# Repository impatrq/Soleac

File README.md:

<!DOCTYPE html>
<html>
<head>
    <meta charset="UTF-8">

</head>
<body>
    <h1><strong>Soleac</strong></h1>
<p align="center">
  
  &nbsp;&nbsp;&nbsp;&nbsp;
  
</p>
    </body> 
  <h2><strong>Logros y Reconocimientos</strong></h2>
<li>🏅 <b>Ganadores del 1° puesto en la categoría Prototipos: Seguridad y Protección - ONIET 2026</b> (puntaje: 90/100)  </li>
📍 Representando a la <b>E.E.S.T. N°7 “Taller Regional Quilmes”</b>, Buenos Aires, Argentina
</body>
  <h2><strong>Organizacion de archivos</strong></h2>
<em><li><b>Carpeta de campo</b>/Progreso y documentacion </li>
<li><b>Diseño 3D</b>/Diseños fisicos de herraminetas</li>
<li><b>Firmware</b>/Codigos implementados a los microcontroladores</li>
<li><b>Hardware</b></Esquematicos y PCBs</li>
<li><b>Assets</b>/Logotipos, README lockup</li></em>
<hr>
<body>
    <h2><strong>Que es Soleac y cómo funciona</strong></h2>
   <em><b>Soleac es un instrumento tecnologico detector de fugas de aire comprimido y gas. 
   <br>Mediante receptores de frecuencia tales cómo:</b>
   <li>Microfono MEMS SPH0641LU4H-1</li>
    <li>MURATA MA40S4R</li>
<b>Podemos captar fugas en caños, ya que estas generan una frecuencia de entre 20khz y 80khz dependiendo el tamaño.<br>Mediante el siguiente sensor:</b>
 <li>Sensor de gas MQ-9</li>
 <b>Al acercar el instrumento, este sensor confirma si realmente hay una fuga, cabe aclarar que solo funciona sensando los siguientes gases:</b>
 <ul>
  <li>Gas Licuado de Petróleo</li>
  <li>Propano</li>
  <li>Metano</li>
  <li>Monóxido de carbono</li>
    <li>butano</li>
</ul>
<b>Si quisieras captar aire comprimido con este sensor, por ejemplo, no sirve y tendrias que usar los sensores de frecuencia.</b></em>
<hr>
<body>
    <h2><strong>Porque existe Soleac</strong></h2>
    <em><b>El instrumento Soleac surge de tres problematicas actuales:</b><br>
    La primera y mas importante es que solo existe una herramienta para los plomeros que les indique con precision donde hay una fuga sin tener que romper ni un ladrillo de pared, la problematica de esta herramienta es que es demasiado cara y ahi es donde entra soleac, presentando un precio que por lo menos este en el presupuesto de un plomero promedio. Llevando a estas herramientas detectores de fugas no solo a empresas grandes, si no tambien a empresas chicas y hogares.</em>
<hr>
<body>
    <h2><strong>Modelo Soleac</strong></h2>

<hr>
<body>
  <h2><strong>Componentes principales del proyecto</strong></h2>
  <em><li>Esp32 S3 Touch Lcd 3.5B</li>
  <li>Microfono MEMS SPH0641LU4H-1</li>
  <li>MURATA MA40S4R</li>
  <li>Sensor de gas MQ-9</li></em>
</body>
<hr>
<body>
    <h2><strong>Integrantes</strong></h2>
  <em><li>Rea Vera Jhonatan</li>
  <li>Solis Tobias</li>
  <li>Sanabria Federico</li>
  <li>Romero Julian</li>
    <li>Paolo Valentino</li></em>
</body>
<hr>

<hr>
<body>
<h3><strong>Contacto</strong></h3>
<p>
  <br>
  <br>
  
    <br>
</p>

<h3><strong>Otros proyectos</strong></h3>
<p>
  
</p>

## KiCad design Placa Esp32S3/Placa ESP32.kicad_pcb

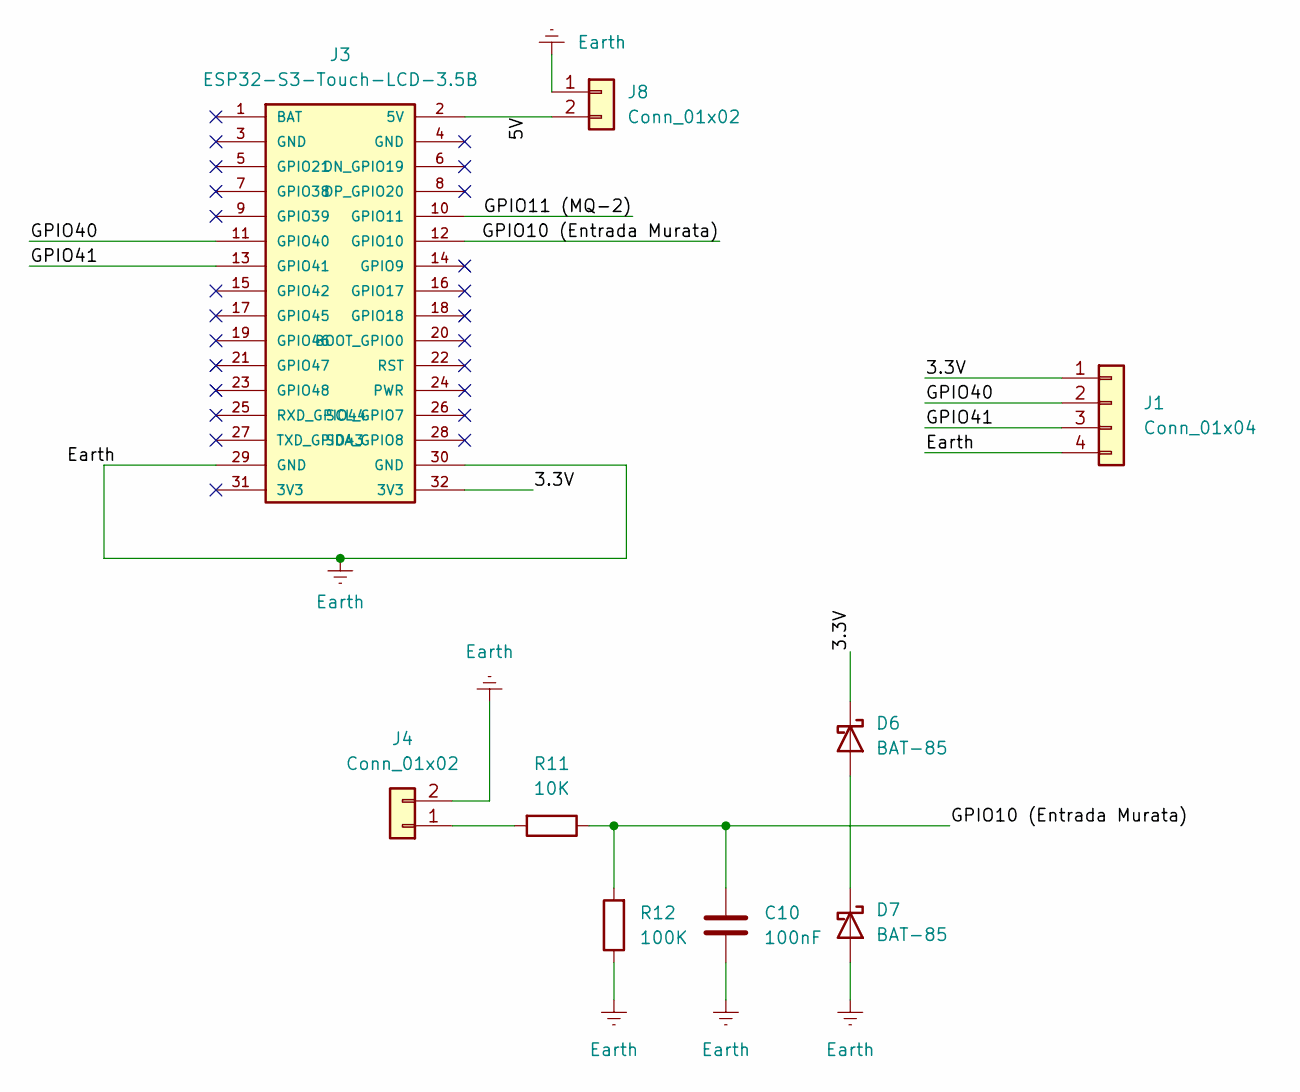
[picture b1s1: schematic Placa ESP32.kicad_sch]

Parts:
C10: 100nF; C_Radial_D6.3mm_H11.0mm_P2.50mm
D6, D7: BAT-85; D_DO-35_SOD27_P7.62mm_Horizontal
J1: Conn_01x04; Molex_KK-254_AE-6410-04A_1x04_P2.54mm_Vertical
J3: ESP32-S3-Touch-LCD-3.5B; ESP32-S3-Touch-LCD-3.5B_Header_2x16_P2.54mm
J4, J8: Conn_01x02; Molex_KK-254_AE-6410-02A_1x02_P2.54mm_Vertical
R11: 10K; R_Axial_DIN0204_L3.6mm_D1.6mm_P7.62mm_Horizontal
R12: 100K; R_Axial_DIN0204_L3.6mm_D1.6mm_P7.62mm_Horizontal

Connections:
/3.3V: D6.1 (K), J1.1, J3.32 (3V3)
/5V: J3.2 (5V), J8.2
/GPIO10 (Entrada Murata): C10.1, J3.12 (GPIO10), R11.1, R12.2
/GPIO11 (MQ-2): J3.10 (GPIO11)
/GPIO40: J1.2, J3.11 (GPIO40)
/GPIO41: J1.3, J3.13 (GPIO41)
Earth: C10.2, D7.2 (A), J1.4, J3.29 (GND), J3.30 (GND), J4.2, J8.1, R12.1
unnamed: D6.2 (A), D7.1 (K)
unnamed: J4.1, R11.2

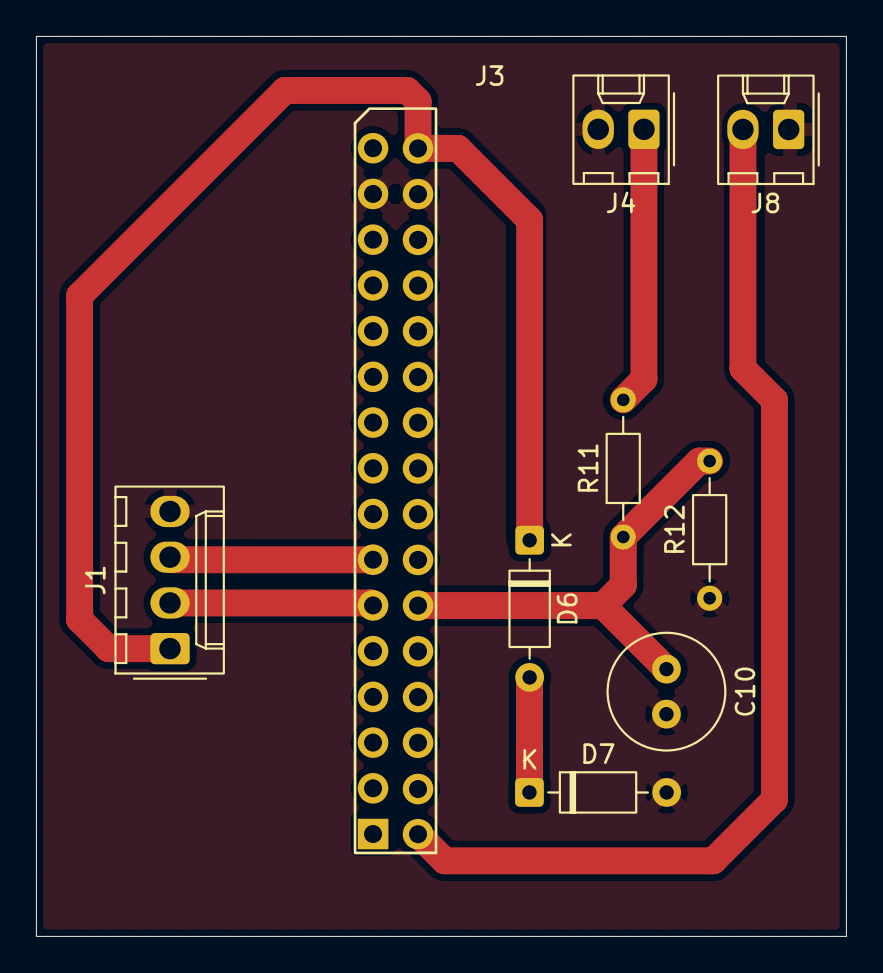
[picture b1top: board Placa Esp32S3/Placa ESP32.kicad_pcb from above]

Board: 2 copper layers, 45.0 x 50.0 mm, 9 parts (0 on the bottom side), 8 nets.

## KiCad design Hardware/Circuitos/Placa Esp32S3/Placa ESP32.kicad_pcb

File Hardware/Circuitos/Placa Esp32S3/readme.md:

## Archivos 
- `Placa ESP32-backups` Backups de la placa ESP32.
- `Placa ESP32.kicad_pcb` PCB formato kicad de la placa ESP32.
- `Placa ESP32.kicad_pro`  configuración compartida entre el editor de esquemáticos y el editor de PCB.
- `Placa ESP32.kicad_sch` diagrama esquemático de la placa ESP32.

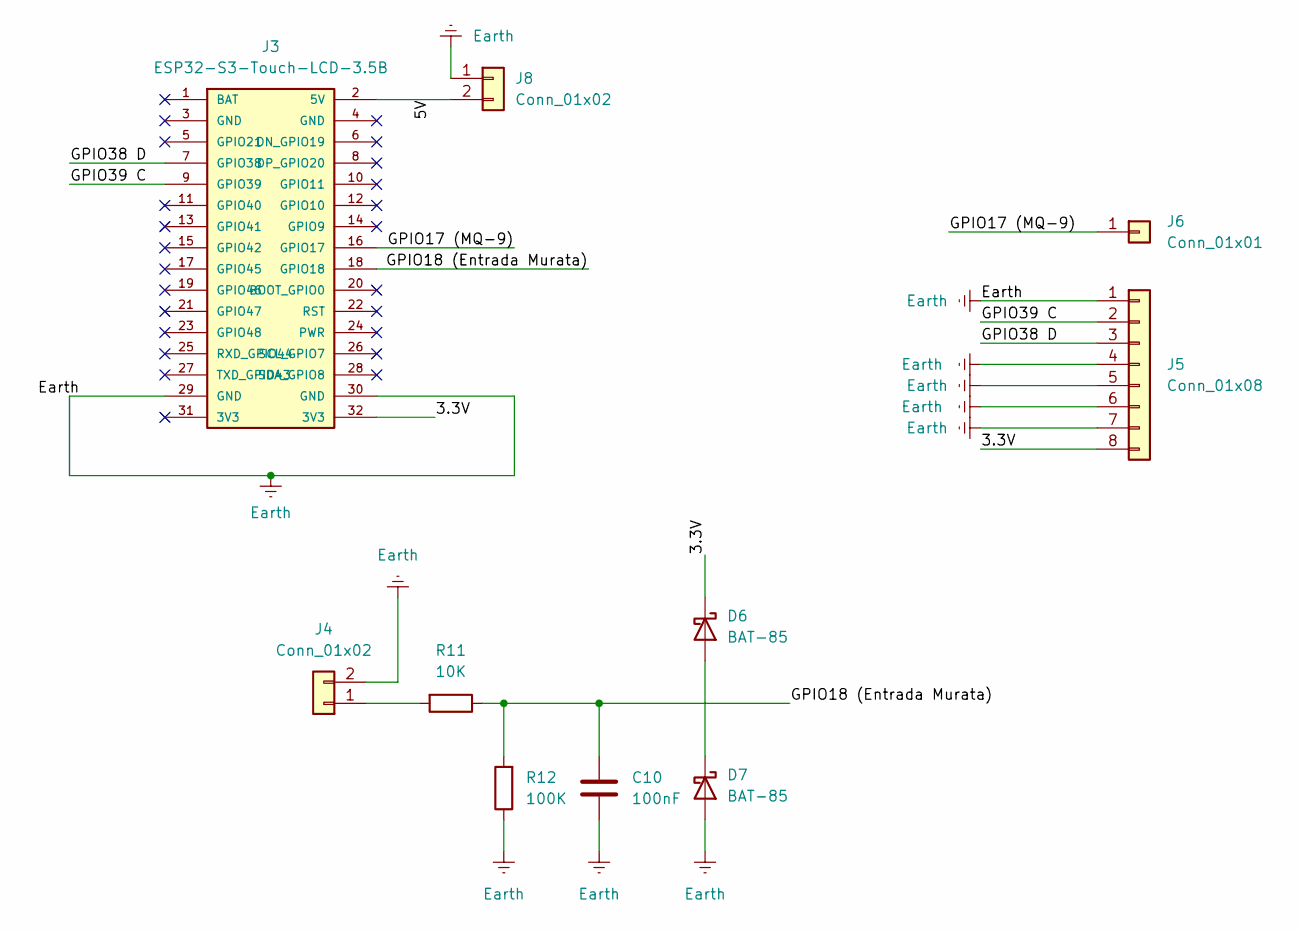
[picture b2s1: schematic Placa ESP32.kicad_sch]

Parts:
C10: 100nF; C_Radial_D6.3mm_H11.0mm_P2.50mm
D6, D7: BAT-85; D_DO-35_SOD27_P7.62mm_Horizontal
J3: ESP32-S3-Touch-LCD-3.5B; ESP32-S3-Touch-LCD-3.5B_Header_2x16_P2.54mm
J4, J8: Conn_01x02; Molex_KK-254_AE-6410-02A_1x02_P2.54mm_Vertical
J5: Conn_01x08; RJ45_Amphenol_54602-x08_Horizontal
J6: Conn_01x01; PinHeader_1x01_P2.00mm_Vertical
R11: 10K; R_Axial_DIN0204_L3.6mm_D1.6mm_P7.62mm_Horizontal
R12: 100K; R_Axial_DIN0204_L3.6mm_D1.6mm_P7.62mm_Horizontal

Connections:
/3.3V: D6.1 (K), J3.32 (3V3), J5.8
/5V: J3.2 (5V), J8.2
/GPIO17 (MQ-9): J3.16 (GPIO17), J6.1 (Pin_1_1)
/GPIO18 (Entrada Murata): C10.1, J3.18 (GPIO18), R11.1, R12.2
/GPIO38 D: J3.7 (GPIO38), J5.3
/GPIO39 C: J3.9 (GPIO39), J5.2
Earth: C10.2, D7.2 (A), J3.29 (GND), J3.30 (GND), J4.2, J5.1, J5.4, J5.5, J5.6, J5.7, J8.1, R12.1
unnamed: D6.2 (A), D7.1 (K)
unnamed: J4.1, R11.2

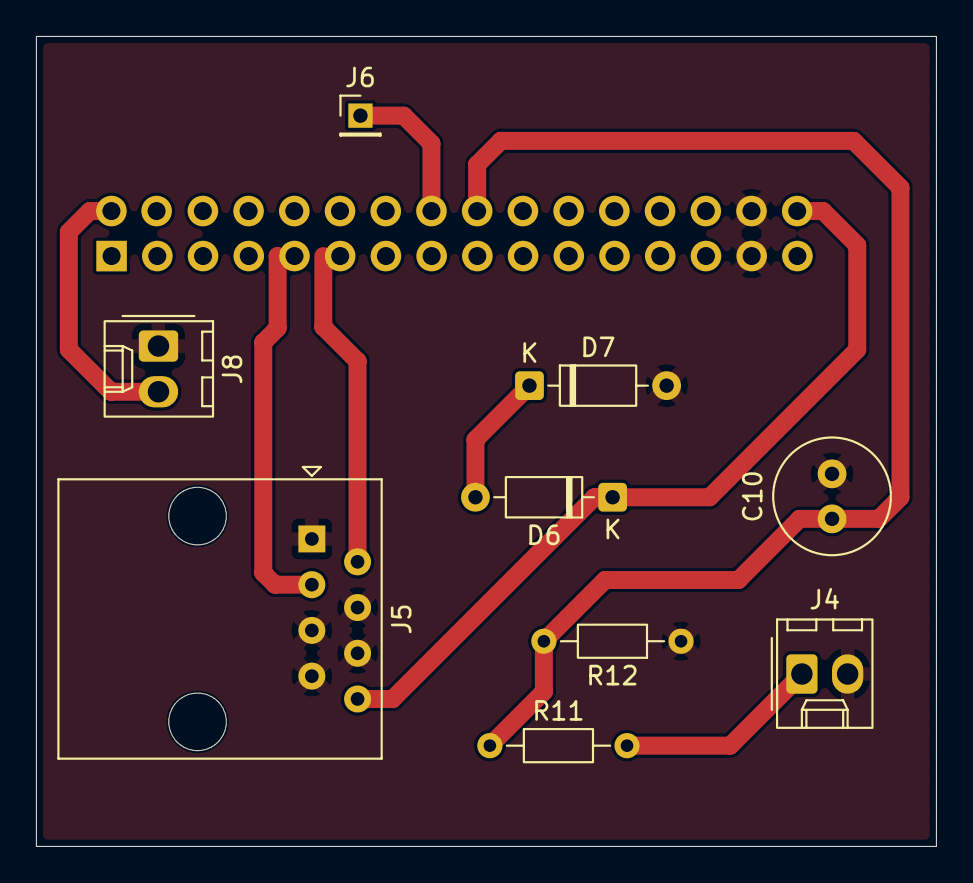
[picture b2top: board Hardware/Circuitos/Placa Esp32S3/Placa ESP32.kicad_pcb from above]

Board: 2 copper layers, 50.0 x 45.0 mm, 10 parts (1 on the bottom side), 9 nets.

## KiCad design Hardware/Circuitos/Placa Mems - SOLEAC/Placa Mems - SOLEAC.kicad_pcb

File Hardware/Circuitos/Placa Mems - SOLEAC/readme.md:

1. Archivos Backups: Historial de copias guardadas de la placa procesadora, placa de microfonos y placa esp32.
2. Remarco de placa de microfonos.
3. Placa de microfonos impresa en pdf.
4. De acá en adelante es el codigo de kicad para generar el pcb.

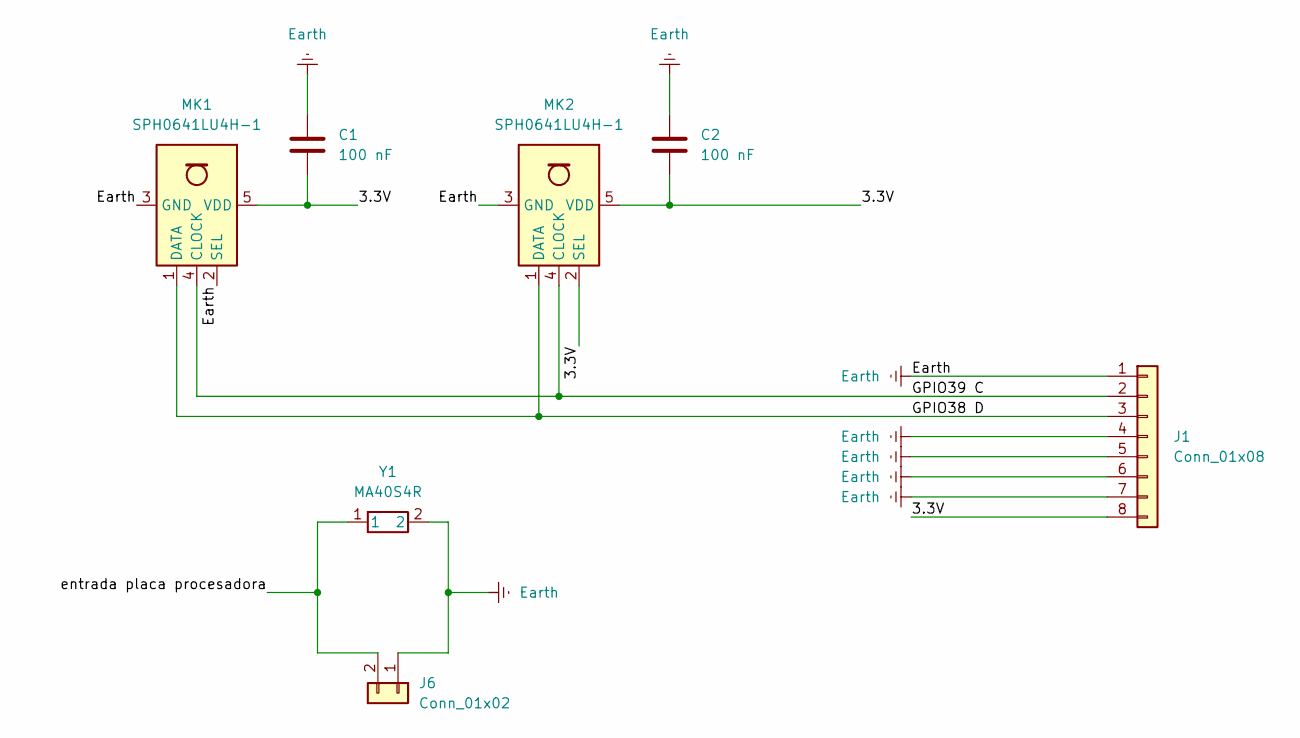
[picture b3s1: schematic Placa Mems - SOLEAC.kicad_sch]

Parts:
C1, C2: 100 nF; C_Disc_D4.3mm_W1.9mm_P5.00mm
J1: Conn_01x08; RJ45_Amphenol_54602-x08_Horizontal
J6: Conn_01x02; Molex_KK-254_AE-6410-02A_1x02_P2.54mm_Vertical
MK1, MK2: SPH0641LU4H-1; Knowles_LGA-5_3.5x2.65mm
Y1: MA40S4R; MA4024R

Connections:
/3.3V: C1.2, C2.2, J1.8, MK1.5 (VDD), MK2.2 (SEL), MK2.5 (VDD)
/GPIO38 D: J1.3, MK1.1 (DATA), MK2.1 (DATA)
/GPIO39 C: J1.2, MK1.4 (CLOCK), MK2.4 (CLOCK)
/entrada placa procesadora: J6.2, Y1.1
Earth: C1.1, C2.1, J1.1, J1.4, J1.5, J1.6, J1.7, J6.1, MK1.2 (SEL), MK1.3 (GND), MK2.3 (GND), Y1.2

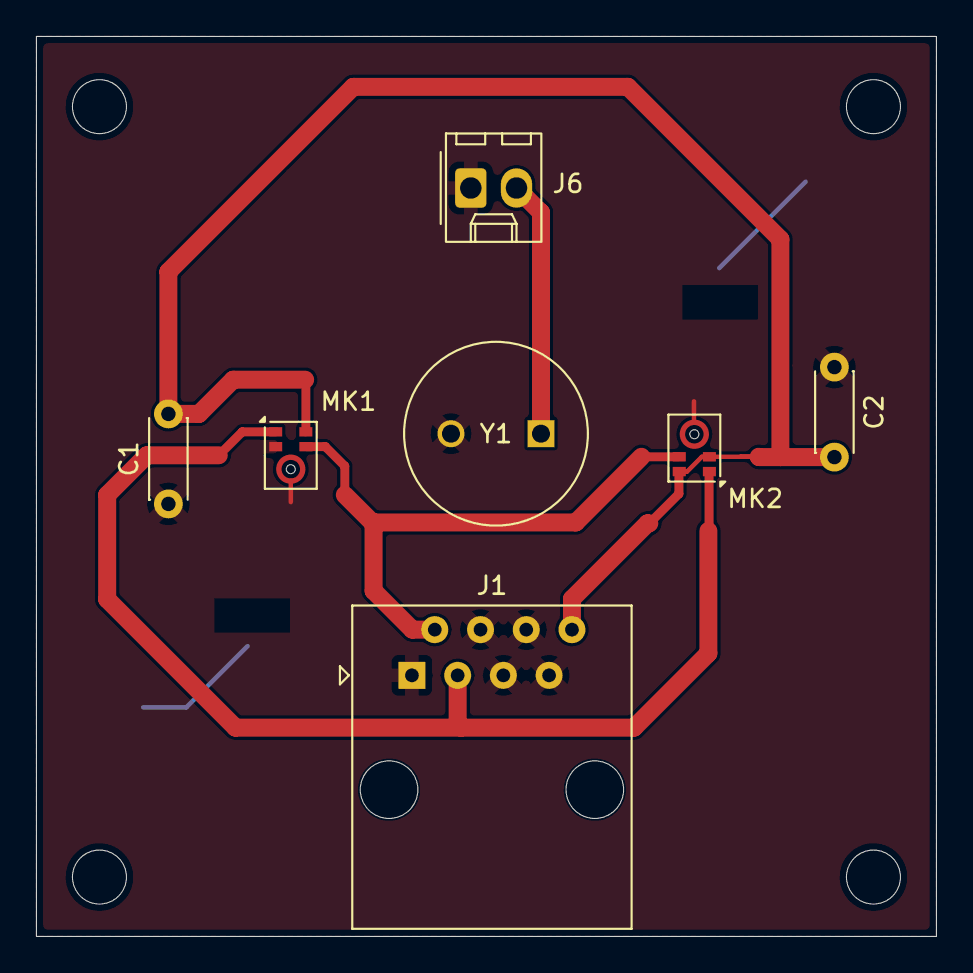
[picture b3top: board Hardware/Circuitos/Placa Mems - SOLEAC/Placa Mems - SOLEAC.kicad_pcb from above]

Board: 2 copper layers, 50.0 x 50.0 mm, 7 parts (0 on the bottom side), 5 nets.

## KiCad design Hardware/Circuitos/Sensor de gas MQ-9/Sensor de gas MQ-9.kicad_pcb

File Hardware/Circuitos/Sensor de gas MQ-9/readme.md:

## Archivos
- `Sensor de gas MQ-9-backups` Backups de la placa MQ-9.
- `Sensor de gas MQ-9.kicad_pcb` PCB formato kicad de la placa MQ-9.
- `Sensor de gas MQ-9.kicad_pro`  configuración compartida entre el editor de esquemáticos y el editor de PCB.
- `Sensor de gas MQ-9.kicad_sch` diagrama esquemático de la placa MQ-9.

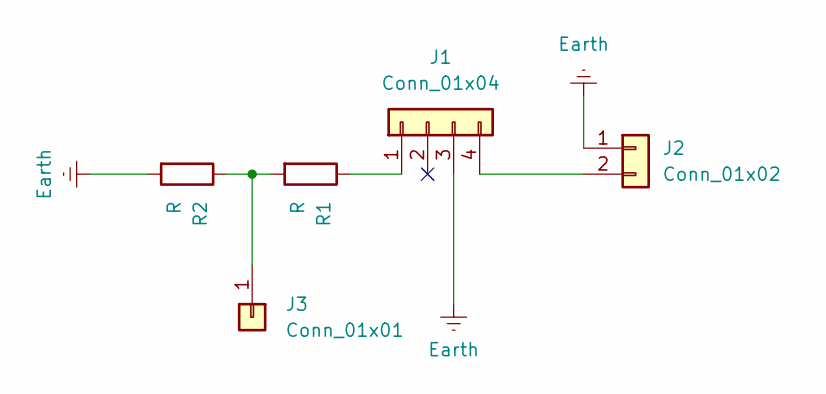
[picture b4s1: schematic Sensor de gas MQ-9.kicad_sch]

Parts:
J1: Conn_01x04; PinHeader_1x04_P2.54mm_Vertical
J2: Conn_01x02; Molex_KK-254_AE-6410-02A_1x02_P2.54mm_Vertical
J3: Conn_01x01; PinHeader_1x01_P2.00mm_Vertical
R1, R2: R; R_Axial_DIN0207_L6.3mm_D2.5mm_P7.62mm_Horizontal

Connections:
Earth: J1.3, J2.1, R2.2
unnamed: J1.1, R1.1
unnamed: J1.4, J2.2
unnamed: J3.1 (Pin_1_1), R1.2, R2.1

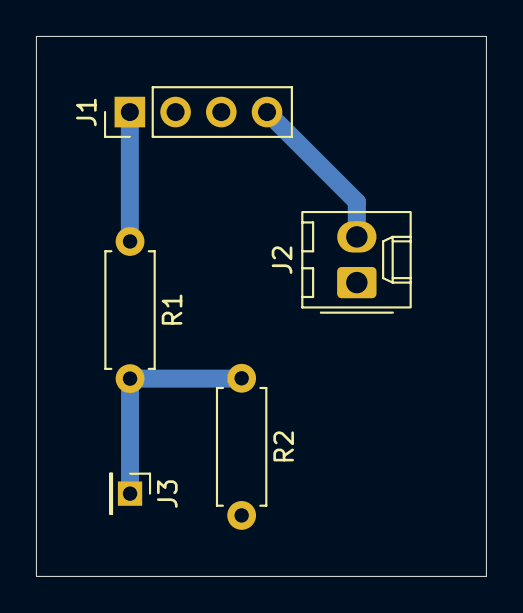
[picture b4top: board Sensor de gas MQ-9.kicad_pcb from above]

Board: 2 copper layers, 25.0 x 30.0 mm, 5 parts (0 on the bottom side), 4 nets.

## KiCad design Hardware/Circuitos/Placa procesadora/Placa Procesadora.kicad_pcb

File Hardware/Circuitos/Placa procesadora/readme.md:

## Archivos
- `Placa Procesadora-backups` Backups de la placa procesadora.
- `Placa Procesadora.kicad_pcb` PCB formato kicad de la placa procesadora.
- `Placa Procesadora.kicad_pro`  configuración compartida entre el editor de esquemáticos y el editor de PCB.
- `Placa Procesadora.kicad_sch` diagrama esquemático de la placa procesadora.

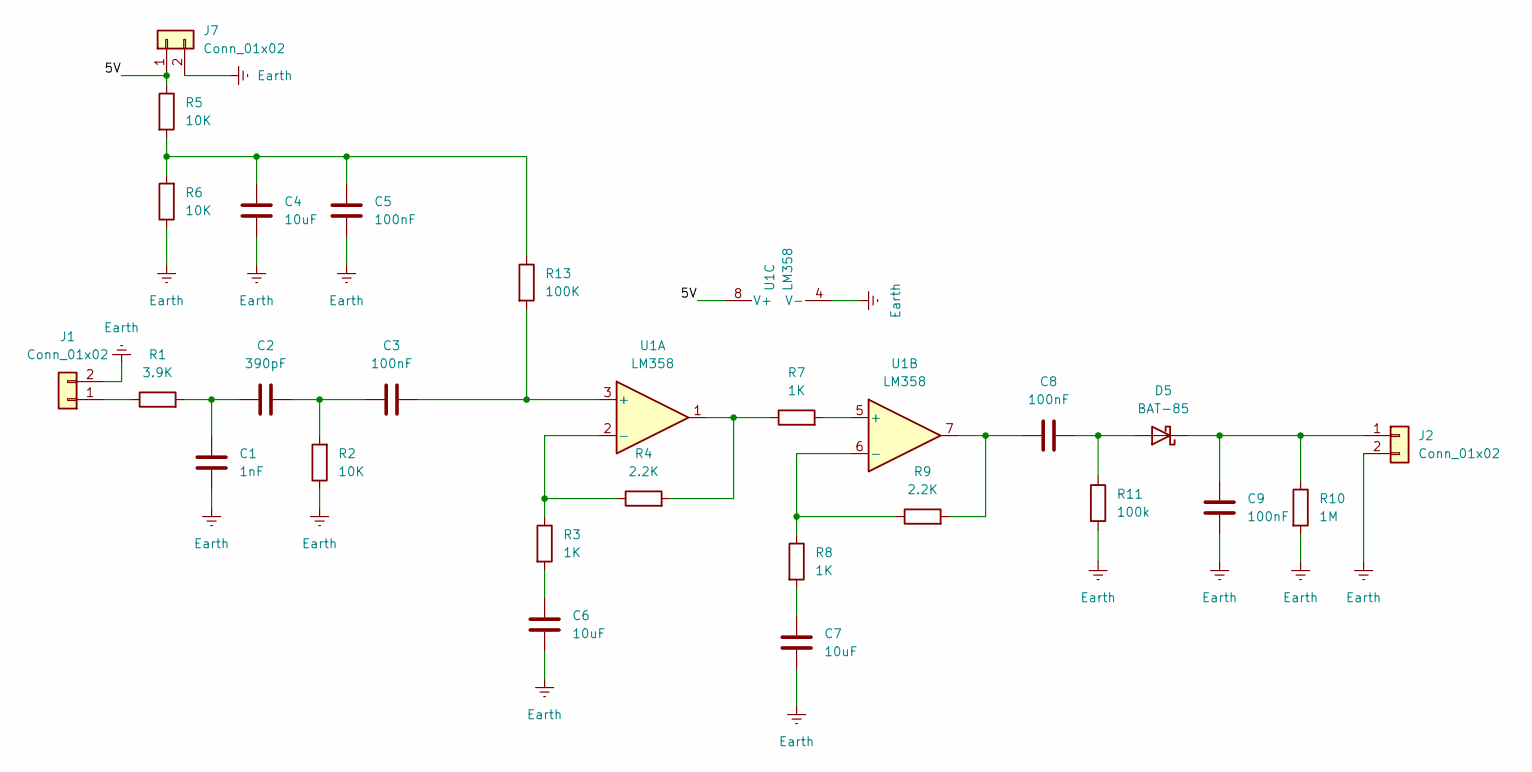
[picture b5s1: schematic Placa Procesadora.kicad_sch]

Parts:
C1: 1nF; C_Radial_D5.0mm_H11.0mm_P2.00mm
C2: 390pF; C_Radial_D5.0mm_H11.0mm_P2.00mm
C3, C5, C8, C9: 100nF; C_Radial_D5.0mm_H11.0mm_P2.00mm
C4, C6, C7: 10uF; C_Radial_D5.0mm_H11.0mm_P2.00mm
D5: BAT-85; D_DO-35_SOD27_P7.62mm_Horizontal
J1, J2, J7: Conn_01x02; Molex_KK-254_AE-6410-02A_1x02_P2.54mm_Vertical
R1: 3.9K; R_Axial_DIN0204_L3.6mm_D1.6mm_P7.62mm_Horizontal
R2, R5, R6: 10K; R_Axial_DIN0204_L3.6mm_D1.6mm_P7.62mm_Horizontal
R3, R7, R8: 1K; R_Axial_DIN0204_L3.6mm_D1.6mm_P7.62mm_Horizontal
R4, R9: 2.2K; R_Axial_DIN0204_L3.6mm_D1.6mm_P7.62mm_Horizontal
R10: 1M; R_Axial_DIN0204_L3.6mm_D1.6mm_P7.62mm_Horizontal
R11: 100k; R_Axial_DIN0204_L3.6mm_D1.6mm_P7.62mm_Horizontal
R13: 100K; R_Axial_DIN0204_L3.6mm_D1.6mm_P7.62mm_Horizontal
U1: LM358

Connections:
/5V: J7.1, R5.1, U1.8 (V+)
Earth: C1.2, C4.2, C5.2, C6.2, C7.2, C9.2, J1.2, J2.2, J7.2, R2.1, R6.1, R10.2, R11.2, U1.4 (V-)
unnamed: C1.1, C2.1, R1.2
unnamed: C2.2, C3.1, R2.2
unnamed: C4.1, C5.1, R5.2, R6.2, R13.1
unnamed: C6.1, R3.2
unnamed: C7.1, R8.2
unnamed: C8.1, R9.2, U1.7
unnamed: C8.2, D5.2 (A), R11.1
unnamed: C9.1, D5.1 (K), J2.1, R10.1
unnamed: J1.1, R1.1
unnamed: R4.2, R7.1, U1.1
unnamed: C3.2, R13.2, U1.3 (+)
unnamed: R3.1, R4.1, U1.2 (-)
unnamed: R7.2, U1.5 (+)
unnamed: R8.1, R9.1, U1.6 (-)

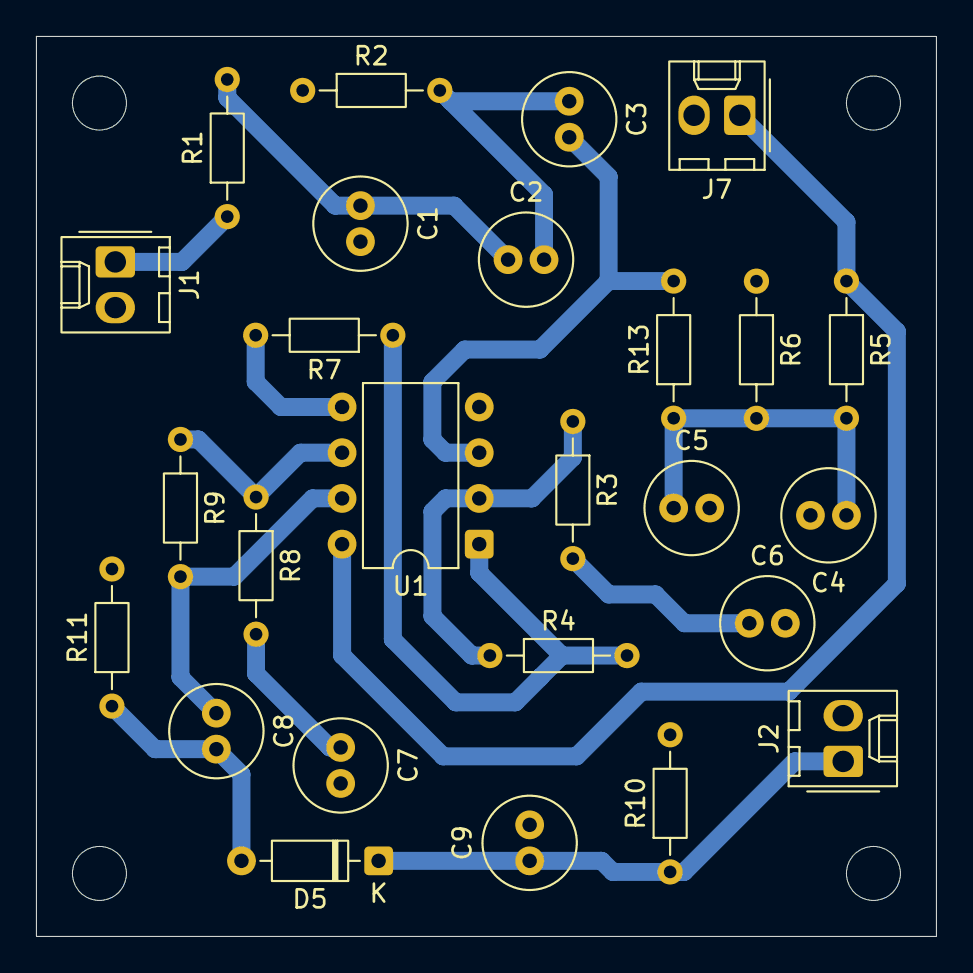
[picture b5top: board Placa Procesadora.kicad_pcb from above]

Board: 2 copper layers, 50.0 x 50.0 mm, 26 parts (0 on the bottom side), 16 nets.

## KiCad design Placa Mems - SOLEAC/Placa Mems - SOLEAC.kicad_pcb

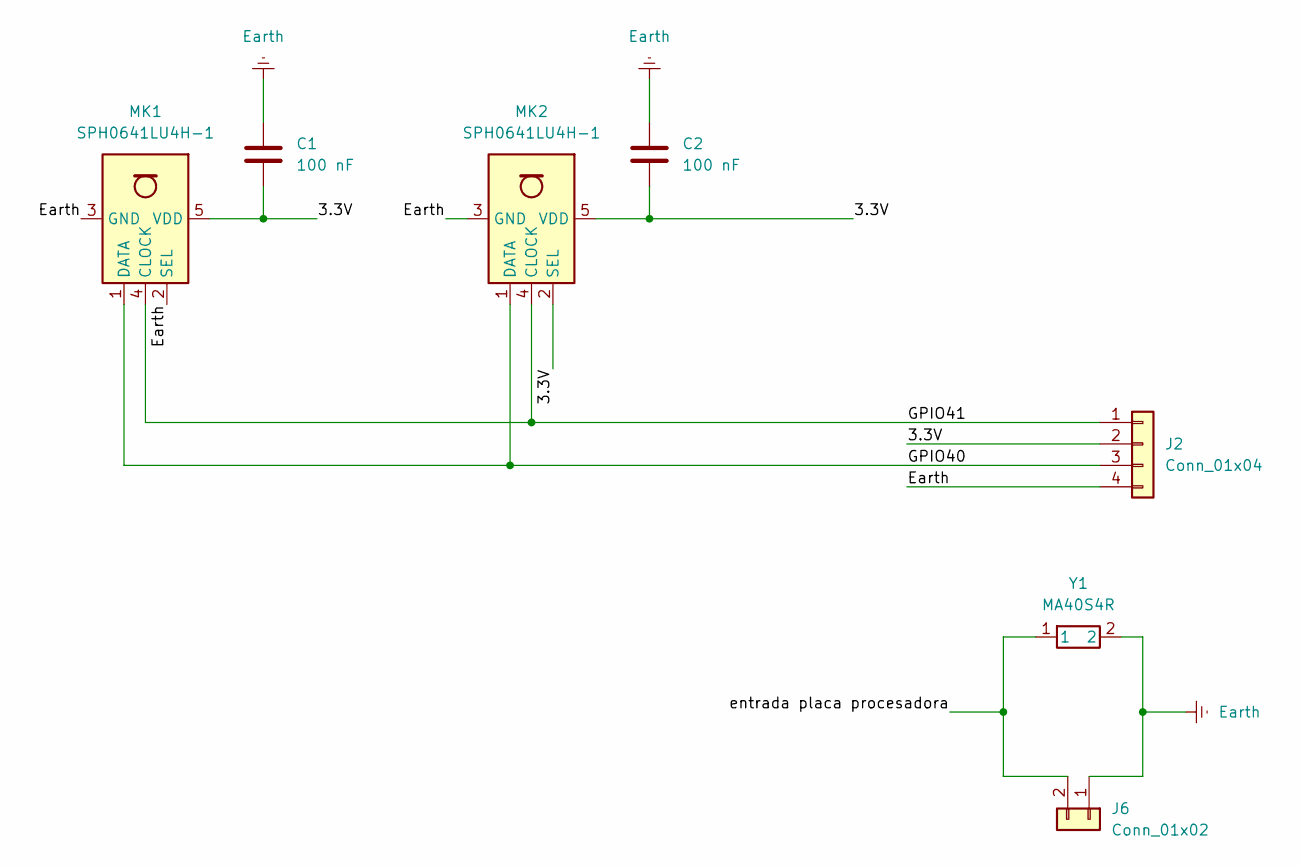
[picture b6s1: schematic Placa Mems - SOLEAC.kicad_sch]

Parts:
C1, C2: 100 nF; C_Disc_D4.3mm_W1.9mm_P5.00mm
J2: Conn_01x04; Molex_KK-254_AE-6410-04A_1x04_P2.54mm_Vertical
J6: Conn_01x02; Molex_KK-254_AE-6410-02A_1x02_P2.54mm_Vertical
MK1, MK2: SPH0641LU4H-1; Knowles_LGA-5_3.5x2.65mm
Y1: MA40S4R; MA4024R

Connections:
/3.3V: C1.2, C2.2, J2.2, MK1.5 (VDD), MK2.2 (SEL), MK2.5 (VDD)
/GPIO40: J2.3, MK1.1 (DATA), MK2.1 (DATA)
/GPIO41: J2.1, MK1.4 (CLOCK), MK2.4 (CLOCK)
/entrada placa procesadora: J6.2, Y1.1
Earth: C1.1, C2.1, J2.4, J6.1, MK1.2 (SEL), MK1.3 (GND), MK2.3 (GND), Y1.2

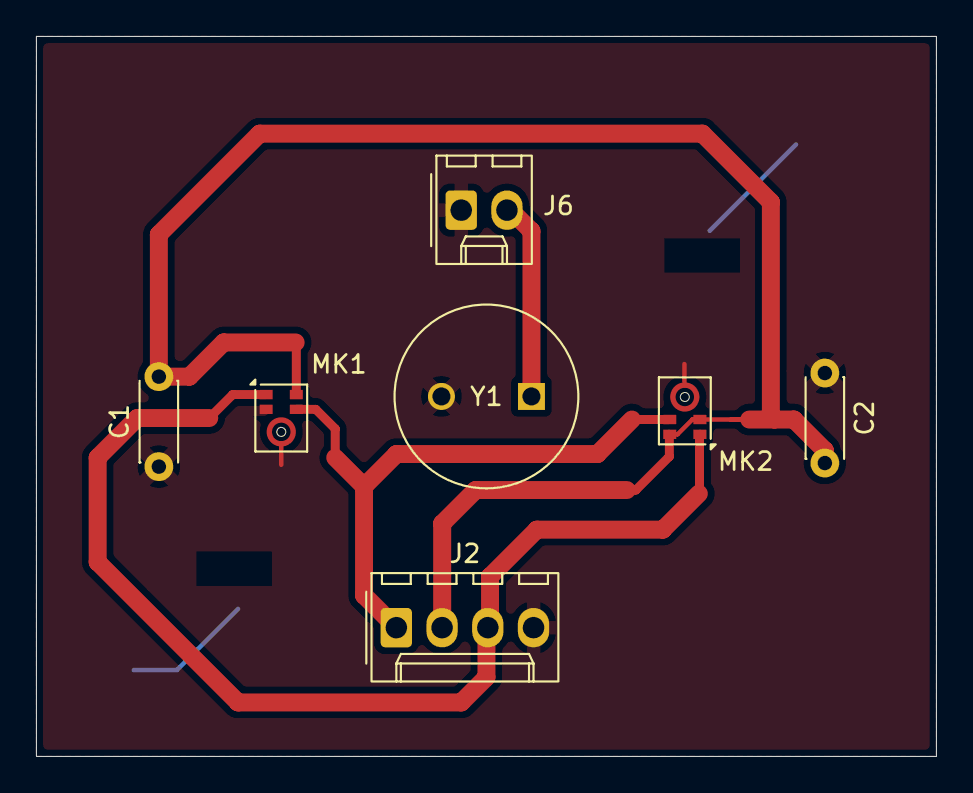
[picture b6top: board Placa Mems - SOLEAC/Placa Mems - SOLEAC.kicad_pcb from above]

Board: 2 copper layers, 50.0 x 40.0 mm, 7 parts (0 on the bottom side), 5 nets.

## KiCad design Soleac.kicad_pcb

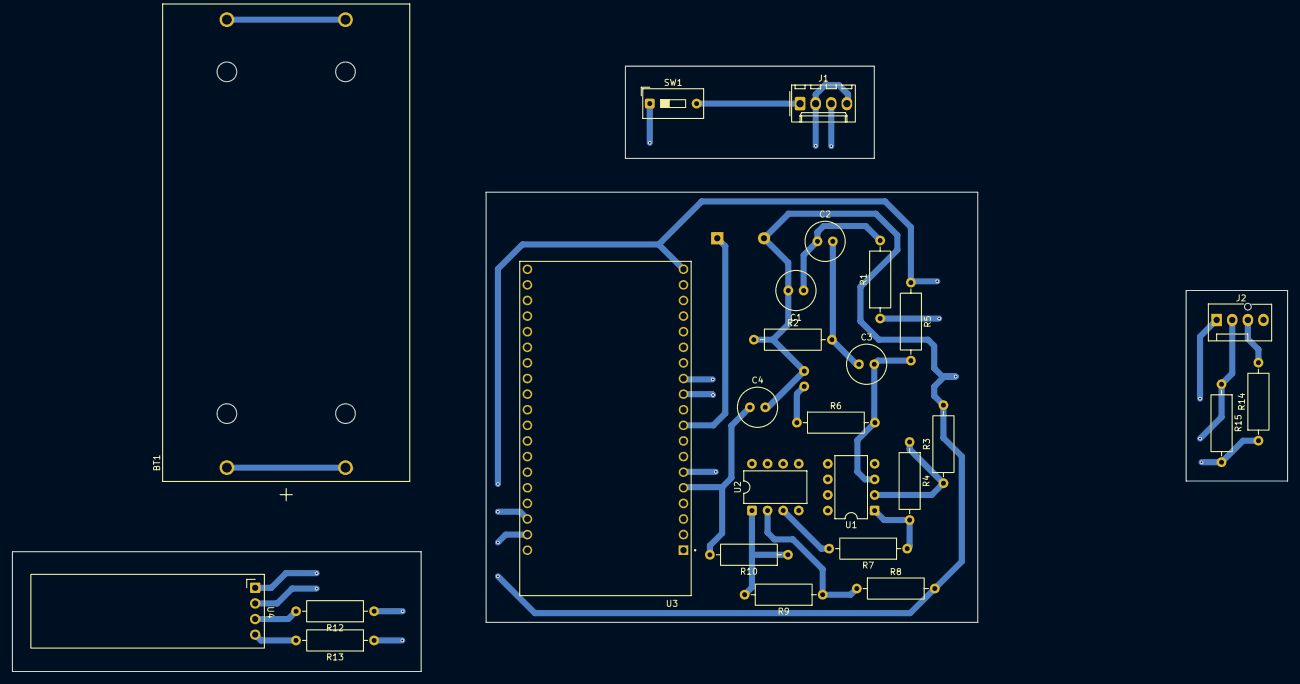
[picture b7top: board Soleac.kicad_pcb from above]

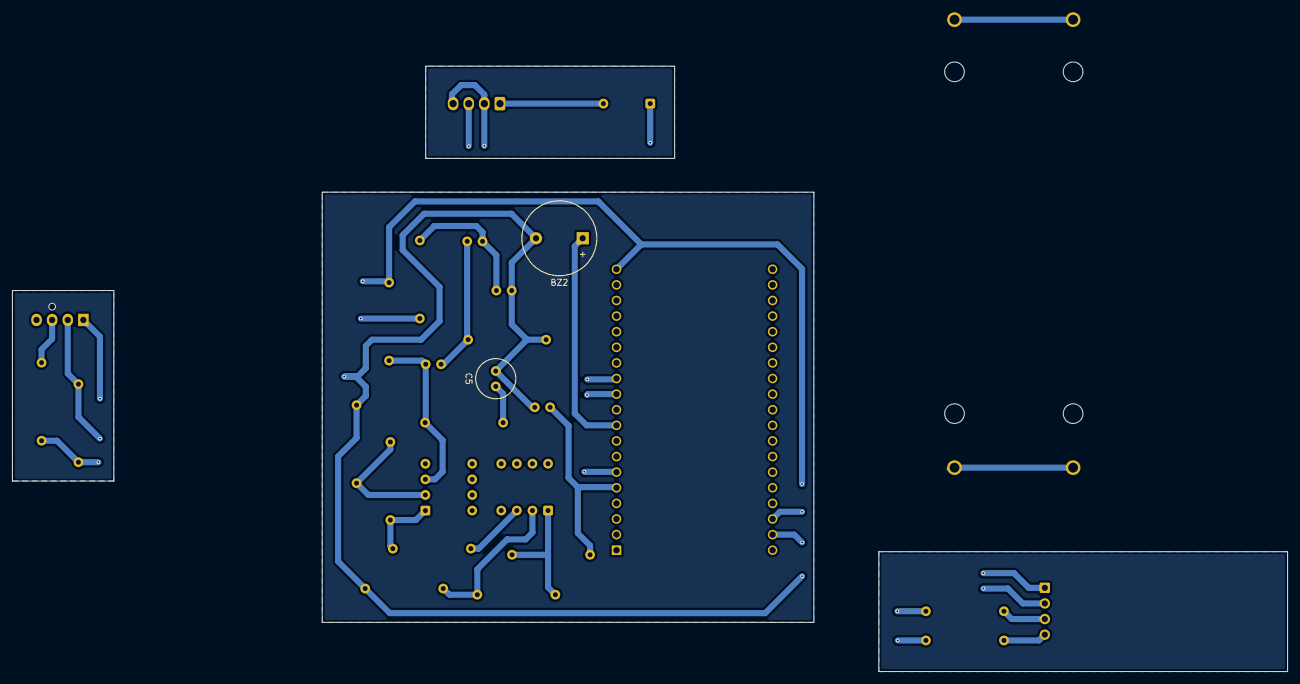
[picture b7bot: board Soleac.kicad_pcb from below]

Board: 2 copper layers, 207.5 x 98.5 mm, 28 parts (2 on the bottom side), 21 nets.

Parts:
BT1: BK-18650-PC4; BAT_BK-18650-PC4
BZ2: Buzzer; Buzzer_12x9.5RM7.6
C1, C2, C3, C4, C5: C; C_Radial_D6.3mm_H7.0mm_P2.50mm
J1: Regulador de voltaje; Molex_KK-254_AE-6410-04A_1x04_P2.54mm_Vertical
J2: Sensor MQ-2; FanPinHeader_1x04_P2.54mm_Vertical
R1, R2, R3, R4, R5, R6, R7, R8, R9, R10, R12, R13, R14, R15: R; R_Axial_DIN0309_L9.0mm_D3.2mm_P12.70mm_Horizontal
SW1: SW_SPST; SW_DIP_SPSTx01_Slide_9.78x4.72mm_W7.62mm_P2.54mm
U1, U2: LM358; DIP-8_W7.62mm
U3: ESP32-DEVKITC-32D; MODULE_ESP32-DEVKITC-32D
U4: ER_OLEDM0.91_1x-I2C

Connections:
/5V: J1.3, J2.1, R5.1, U3.J2-19 (EXT_5V), U4.2 (VCC)
/GPIO22 (SCL OLED): R12.1, U3.J3-3 (IO22)
/GPIO23 (SDA OLED): R13.1, U3.J3-2 (IO23)
/GPIO25 (BUZZER): BZ2.1 (+), U3.J2-9 (IO25)
/GPIO35 (MQ-2): R14.1, R15.2, U3.J2-6 (IO35)
Earth: BT1.1-, BT1.2-, BZ2.2 (-), C1.2, C4.2, C5.2, J1.2, J1.4, J2.2, R2.1, R3.2, R8.2, R15.1, U4.1 (GND)
unnamed: C1.1, C2.1, R1.2
unnamed: C2.2, C3.1, R2.2
unnamed: C5.1, R6.1
unnamed: J1.1, SW1.2 (B)
unnamed: J2.3, R14.2
unnamed: R4.2, R7.1, U1.1
unnamed: R9.2, R10.1, U2.1
unnamed: BT1.1+, BT1.2+, SW1.1 (A)
unnamed: C3.2, R5.2, R6.2, U1.3 (+)
unnamed: R3.1, R4.1, U1.2 (-)
unnamed: R7.2, U2.3 (+)
unnamed: R8.1, R9.1, U2.2 (-)
unnamed: C4.1, R10.2, U3.J2-5 (IO34)
unnamed: R12.2, U4.3 (SCL)
unnamed: R13.2, U4.4 (SDA)

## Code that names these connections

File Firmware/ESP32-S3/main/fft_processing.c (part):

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#define PIN_BUZZER GPIO_NUM_NC
#define PIN_LED GPIO_NUM_NC
#define PIN_BOOT_BUTTON GPIO_NUM_0
// Prueba solicitada intercambiando los roles: CLK=GPIO39 y DATA=GPIO38.
#define I2S_CLK_PIN GPIO_NUM_39
#define I2S_DATA_PIN GPIO_NUM_38
#define PDM_SENSOR_SLOT_PREFERRED I2S_PDM_SLOT_LEFT
// GPIO9/10/11 pertenecen al bus de la microSD integrado en la Waveshare.
// GPIO17 y GPIO18 están expuestos en el header y son entradas ADC2 en el S3.
#define MQ9_ADC_GPIO GPIO_NUM_17
#define MA40_ADC_GPIO GPIO_NUM_18
// El MA40S4R no está instalado actualmente. Cambiar a 1 al conectarlo.
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    }

    // En esta placa GPIO9/10/11 están reservados por la microSD y los demás
    // GPIO ADC1 están ocupados por LCD/I2C. GPIO18 es ADC2; ESP-IDF protege
    // las lecturas frente a Wi-Fi. La aplicación usa BLE, no Wi-Fi.

    /* MQ-9 y MA40S4R comparten la misma unidad ADC1. */
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        pdm_test_bytes == sizeof(pdm_slot_test_buffer) &&
        validar_bloque_pdm(pdm_slot_test_buffer, pdm_test_bytes,
                           &probe_unos_pct, &probe_transiciones_pct);
    ESP_LOGI(TAG, "PDM probe DIN=GPIO38 CLK=GPIO39 slot=LEFT(SELECT=GND): %s unos=%.1f%% trans=%.1f%% (%s %u/%u bytes)",
             slot_valido ? "DATOS VALIDOS" : "sin actividad PDM",
             probe_unos_pct,
             probe_transiciones_pct,
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                right_bytes == sizeof(pdm_slot_test_buffer) &&
                validar_bloque_pdm(pdm_slot_test_buffer, right_bytes,
                                   &right_unos_pct, &right_transiciones_pct);
            ESP_LOGI(TAG, "PDM probe DIN=GPIO38 CLK=GPIO39 slot=RIGHT: %s unos=%.1f%% trans=%.1f%% (%s %u/%u bytes); warmup=%u",
                     right_valido ? "DATOS VALIDOS" : "sin actividad PDM",
                     right_unos_pct, right_transiciones_pct,
                     esp_err_to_name(right_read_ret), (unsigned)right_bytes,
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        }

        if (!slot_valido) {
            ESP_LOGE(TAG, "GPIO38 sigue sin PDM valido con CLK en GPIO39, ni LEFT ni RIGHT");
        }
    }
    if (pdm_datos_iniciales != NULL) {
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
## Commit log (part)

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2026-04-15 medidas de la antena
2026-05-15 Circuitos
2026-05-15 conexiones en el PCB
2026-05-15 Conexión Completa
2026-05-20 Separación de PCBs
2026-05-20 Conexión entre placas
2026-05-21 kicad
2026-05-29 Colocación de base
2026-05-29 Colocación de soporte del mango
2026-05-29 Colocación de mango
2026-05-29 Colocación del segundo soporte
2026-05-29 Colocación de la zona de la pantalla OLED
2026-05-29 Colocación de soporte de la pantalla OLED
2026-06-09 feat: implementar codigo de interfaz a la app movil Soleac
